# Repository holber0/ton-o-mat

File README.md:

# ton-O-mat
 ton-O-mat is a Interatcive sound generator that allows Kids to learn the one scale
 
## Inititial Setup
Enable SPI Bus:
```
sudo nano /boot/config.txt
```
Add following at the end of the File:
```
device_tree_param=spi=on
dtoverlay=spi-bcm2708
```
\
use `sudo raspi-config` to Enable „Advanced Options“ > „SPI“ restart afterwards `sudo reboot now`

## fluidsynth

fluidsynth is need as a background Service prividing a Midi Port for Pyton
```
fluidsynth -a alsa -m alsa_seq -i -l -s -g 1.0 /usr/share/sounds/sf2/FluidR3_GM.sf2
```

## Pyton Settings
\
the Virtual env "env" is used in ths Repo. Use `pip -r requirements.txt` to install all requirements\
if not install:
 
 ```
pip3 install virtualenv
pip install spidev
pip install mfrc522
 ```

source the activate file to switch to the venv 
```
source env/bin/activate
```

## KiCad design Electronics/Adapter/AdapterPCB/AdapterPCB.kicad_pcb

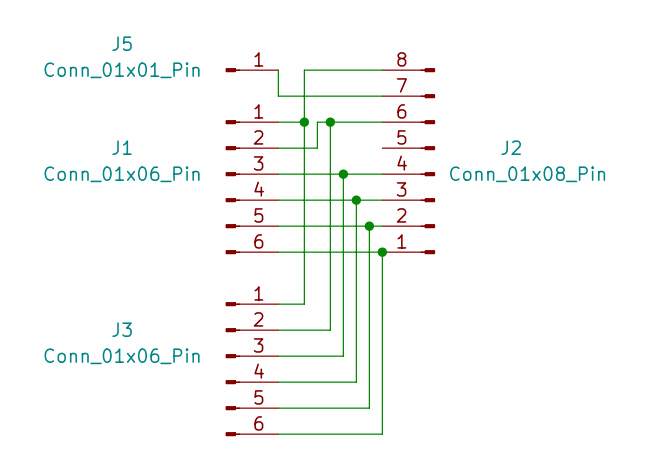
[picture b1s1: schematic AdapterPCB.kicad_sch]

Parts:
J1, J3: Conn_01x06_Pin; PinHeader_1x06_P2.54mm_Vertical
J2: Conn_01x08_Pin; PinHeader_1x08_P2.54mm_Vertical
J5: Conn_01x01_Pin; PinHeader_1x01_P2.54mm_Vertical

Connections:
unnamed: J1.1, J2.8, J3.1
unnamed: J1.2, J2.6, J3.2
unnamed: J1.3, J2.4, J3.3
unnamed: J1.4, J2.3, J3.4
unnamed: J1.5, J2.2, J3.5
unnamed: J1.6, J2.1, J3.6
unnamed: J2.7, J5.1

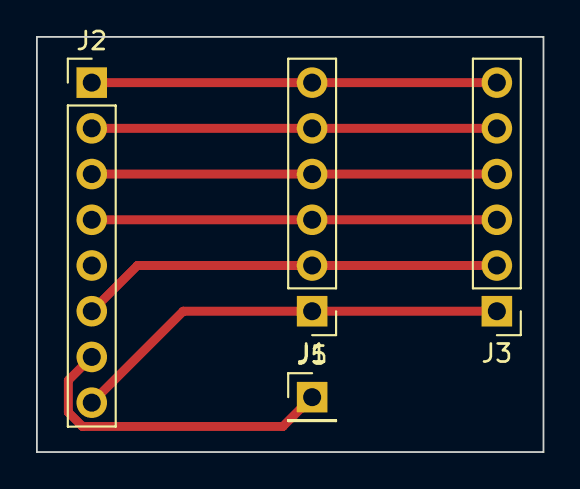
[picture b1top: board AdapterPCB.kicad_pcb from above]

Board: 2 copper layers, 28.1 x 23.1 mm, 4 parts (0 on the bottom side), 7 nets.

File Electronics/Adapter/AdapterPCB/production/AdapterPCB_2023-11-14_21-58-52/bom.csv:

Designator,Footprint,Quantity,Value,LCSC Part #
"J1, J3",PinHeader_1x06_P2.54mm_Vertical,2,Conn_01x06_Pin,
J2,PinHeader_1x08_P2.54mm_Vertical,1,Conn_01x08_Pin,
J5,PinHeader_1x01_P2.54mm_Vertical,1,Conn_01x01_Pin,

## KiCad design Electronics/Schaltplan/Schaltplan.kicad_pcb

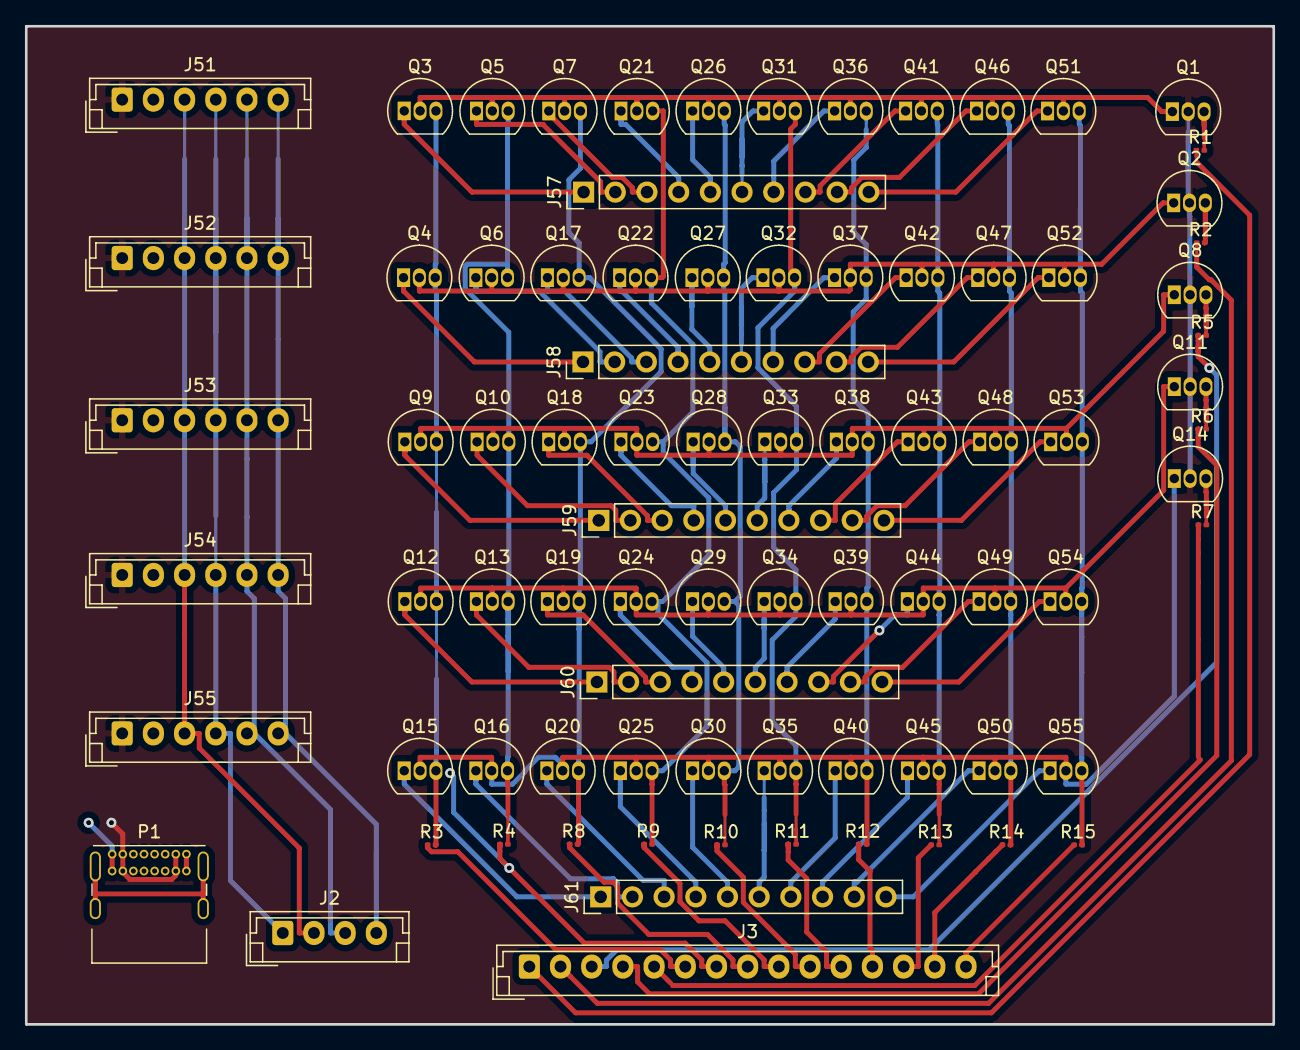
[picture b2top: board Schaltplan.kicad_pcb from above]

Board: 2 copper layers, 100.0 x 80.0 mm, 83 parts (0 on the bottom side), 91 nets.

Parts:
J2: Conn_01x04_Socket; JST_EH_B4B-EH-A_1x04_P2.50mm_Vertical
J3: Conn_01x15_Socket; JST_EH_B15B-EH-A_1x15_P2.50mm_Vertical
J51, J52, J53, J54, J55: Conn_01x06_Socket; JST_EH_B6B-EH-A_1x06_P2.50mm_Vertical
J57, J58, J59, J60, J61: Conn_01x10_Socket; PinHeader_1x10_P2.54mm_Vertical
P1: USB_C_Plug; USB_C_Receptacle_GCT_USB4085
Q1, Q2, Q3, Q4, Q5, Q6, Q7, Q8, Q9, Q10, Q11, Q12, Q13, Q14, Q15, Q16, Q17, Q18, Q19, Q20, Q21, Q22, Q23, Q24, Q25, Q26, Q27, Q28, Q29, Q30, Q31, Q32, Q33, Q34, Q35, Q36, Q37, Q38, Q39, Q40, Q41, Q42, Q43, Q44, Q45, Q46, Q47, Q48, Q49, Q50, Q51, Q52, Q53, Q54, Q55: 2SC1815; TO-92_Inline
R1, R2, R3, R4, R5, R6, R7, R8, R9, R10, R11, R12, R13, R14, R15: R; R_0201_0603Metric

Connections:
3,3V: J51.1, J52.1, J53.1, J54.1, J55.1, P1.A4 (VBUS), P1.A9 (VBUS), P1.B4 (VBUS), P1.B9 (VBUS), Q1.2 (C), Q2.2 (C), Q8.2 (C), Q11.2 (C), Q14.2 (C)
GND: J51.2, J52.2, J53.2, J54.2, J55.2, P1.A1 (GND), P1.A12 (GND), P1.B1 (GND), P1.B12 (GND)
GPIO00: J3.1, R1.1
GPIO01: J3.2, R2.1
GPIO02: J3.3, R5.1
GPIO03: J3.4, R6.1
GPIO04: J3.5, R7.1
GPIO05: J3.6, R3.1
GPIO06: J3.7, R4.1
GPIO07: J3.8, R8.1
GPIO08: J3.9, R9.1
GPIO09: J3.10, R10.1
GPIO10: J3.11, R11.1
GPIO11: J3.12, R12.1
GPIO12: J3.13, R13.1
GPIO13: J3.14, R14.1
GPIO14: J3.15, R15.1
MISO: J2.2, J51.3, J52.3, J53.3, J54.3, J55.3
MOSI: J2.1, J51.4, J52.4, J53.4, J54.4, J55.4
unnamed: Q1.3 (B), R1.2
unnamed: Q1.1 (E), Q3.2 (C), Q5.2 (C), Q7.2 (C), Q21.2 (C), Q26.2 (C), Q31.2 (C), Q36.2 (C), Q41.2 (C), Q46.2 (C), Q51.2 (C)
unnamed: Q2.3 (B), R2.2
unnamed: Q8.3 (B), R5.2
unnamed: Q5.3 (B), Q6.3 (B), Q10.3 (B), Q13.3 (B), Q16.3 (B), R4.2
unnamed: Q8.1 (E), Q9.2 (C), Q10.2 (C), Q18.2 (C), Q23.2 (C), Q28.2 (C), Q33.2 (C), Q38.2 (C), Q43.2 (C), Q48.2 (C), Q53.2 (C)
unnamed: Q11.3 (B), R6.2
unnamed: Q11.1 (E), Q12.2 (C), Q13.2 (C), Q19.2 (C), Q24.2 (C), Q29.2 (C), Q34.2 (C), Q39.2 (C), Q44.2 (C), Q49.2 (C), Q54.2 (C)
unnamed: Q3.3 (B), Q4.3 (B), Q9.3 (B), Q12.3 (B), Q15.3 (B), R3.2
unnamed: Q14.3 (B), R7.2
unnamed: Q14.1 (E), Q15.2 (C), Q16.2 (C), Q20.2 (C), Q25.2 (C), Q30.2 (C), Q35.2 (C), Q40.2 (C), Q45.2 (C), Q50.2 (C), Q55.2 (C)
unnamed: Q7.3 (B), Q17.3 (B), Q18.3 (B), Q19.3 (B), Q20.3 (B), R8.2
unnamed: Q2.1 (E), Q4.2 (C), Q6.2 (C), Q17.2 (C), Q22.2 (C), Q27.2 (C), Q32.2 (C), Q37.2 (C), Q42.2 (C), Q47.2 (C), Q52.2 (C)
unnamed: Q21.3 (B), Q22.3 (B), Q23.3 (B), Q24.3 (B), Q25.3 (B), R9.2
unnamed: Q26.3 (B), Q27.3 (B), Q28.3 (B), Q29.3 (B), Q30.3 (B), R10.2
unnamed: Q31.3 (B), Q32.3 (B), Q33.3 (B), Q34.3 (B), Q35.3 (B), R11.2
unnamed: Q36.3 (B), Q37.3 (B), Q38.3 (B), Q39.3 (B), Q40.3 (B), R12.2
unnamed: Q41.3 (B), Q42.3 (B), Q43.3 (B), Q44.3 (B), Q45.3 (B), R13.2
unnamed: Q46.3 (B), Q47.3 (B), Q48.3 (B), Q49.3 (B), Q50.3 (B), R14.2
unnamed: Q51.3 (B), Q52.3 (B), Q53.3 (B), Q54.3 (B), Q55.3 (B), R15.2
RST01: J57.1, Q3.1 (E)
RST02: J57.2, Q5.1 (E)
RST03: J57.3, Q7.1 (E)
RST04: J57.4, Q21.1 (E)
RST05: J57.5, Q26.1 (E)
RST06: J57.6, Q31.1 (E)
RST07: J57.7, Q36.1 (E)
RST08: J57.8, Q41.1 (E)
RST09: J57.9, Q46.1 (E)
RST10: J57.10, Q51.1 (E)
RST11: J58.1, Q4.1 (E)
RST12: J58.2, Q6.1 (E)
RST13: J58.3, Q17.1 (E)
RST14: J58.4, Q22.1 (E)
RST15: J58.5, Q27.1 (E)
RST16: J58.6, Q32.1 (E)
RST17: J58.7, Q37.1 (E)
RST18: J58.8, Q42.1 (E)
RST19: J58.9, Q47.1 (E)
RST20: J58.10, Q52.1 (E)
RST21: J59.1, Q9.1 (E)
RST22: J59.2, Q10.1 (E)
RST23: J59.3, Q18.1 (E)
RST24: J59.4, Q23.1 (E)
RST25: J59.5, Q28.1 (E)
RST26: J59.6, Q33.1 (E)
RST27: J59.7, Q38.1 (E)
RST28: J59.8, Q43.1 (E)
RST29: J59.9, Q48.1 (E)
RST30: J59.10, Q53.1 (E)
RST31: J60.1, Q12.1 (E)
RST32: J60.2, Q13.1 (E)
RST33: J60.3, Q19.1 (E)
RST34: J60.4, Q24.1 (E)
RST35: J60.5, Q29.1 (E)
RST36: J60.6, Q34.1 (E)
RST37: J60.7, Q39.1 (E)
RST38: J60.8, Q44.1 (E)
RST39: J60.9, Q49.1 (E)
RST40: J60.10, Q54.1 (E)
RST41: J61.1, Q15.1 (E)
RST42: J61.2, Q16.1 (E)
RST43: J61.3, Q20.1 (E)
RST44: J61.4, Q25.1 (E)
RST45: J61.5, Q30.1 (E)
RST46: J61.6, Q35.1 (E)
RST47: J61.7, Q40.1 (E)
RST48: J61.8, Q45.1 (E)
RST49: J61.9, Q50.1 (E)
RST50: J61.10, Q55.1 (E)
SCK: J2.3, J51.5, J52.5, J53.5, J54.5, J55.5
SDA: J2.4, J51.6, J52.6, J53.6, J54.6, J55.6

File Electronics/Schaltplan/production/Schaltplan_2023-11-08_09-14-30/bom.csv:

Designator,Footprint,Quantity,Value,LCSC Part #
J2,JST_EH_B4B-EH-A_1x04_P2.50mm_Vertical,1,Conn_01x04_Socket,
J3,JST_EH_B15B-EH-A_1x15_P2.50mm_Vertical,1,Conn_01x15_Socket,
"J51, J52, J53, J54, J55",JST_EH_B6B-EH-A_1x06_P2.50mm_Vertical,5,Conn_01x06_Socket,
"J57, J58, J59, J60, J61",PinHeader_1x10_P2.54mm_Vertical,5,Conn_01x10_Socket,
P1,USB_C_Receptacle_GCT_USB4085,1,USB_C_Plug,
"Q1, Q10, Q11, Q12, Q13, Q14, Q15, Q16, Q17, Q18, Q19, Q2, Q20, Q21, Q22, Q23, Q24, Q25, Q26, Q27, Q28, Q29, Q3, Q30, Q31, Q32, Q33, Q34, Q35, Q36, Q37, Q38, Q39, Q4, Q40, Q41, Q42, Q43, Q44, Q45, Q46, Q47, Q48, Q49, Q5, Q50, Q51, Q52, Q53, Q54, Q55, Q6, Q7, Q8, Q9",TO-92_Inline,55,2SC1815,
"R1, R10, R11, R12, R13, R14, R15, R2, R3, R4, R5, R6, R7, R8, R9",0201,15,R,

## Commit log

2023-09-22 init commit
2023-09-22 added Readme
2023-09-26 added venv and requirements.txt
2023-10-03 first try to use multipe readers
2023-10-03 dummy schaltung zwiwschen den readern
2023-10-04 added Matrix Support to Read Chips
2023-10-04 fixed Matrix to use Raspi default GPIOs
2023-10-04 fixed Import bug
2023-10-04 performance tuning
2023-10-04 added Debug opption
2023-10-04 fixed Typo
2023-10-10 added config File vor Setting
2023-10-10 added MP3 Assets
2023-10-10 first try to get the sound Logic
2023-10-11 added Tone Selector
2023-10-11 added play sound
2023-11-06 changed Config
2023-11-06 Added Python Play Sound
2023-11-06 Integrated PlaySound to Main
2023-11-06 Fixed Config Naming
2023-11-06 change Col by Col Read
2023-11-06 fixed Michi fault
2023-11-06 change palySound to use a background Service
2023-11-06 pip freeze
2023-11-06 README
2023-11-06 added Launch File for autostart via crontab
2023-11-06 fixed unused Deps
2023-11-07 first try to use local mp3s
2023-11-07 local soundfiles
2023-11-07 added local mp3 Files
2023-11-07 fixed direct mp3 play
2023-11-07 added RFID IDs
2023-11-07 Noten hochgeladen
    Noten sind bestellt und werden mit SLS aus Nylon gedruckt.
2023-12-02 Raspi is working with adruino
2023-12-02 added Adruino Code that must run on a Mega
2023-12-08 added autostoart and fixed Int to string
2023-12-08 auto restart, fixing open files error
2023-12-08 fixed Pin Order
2023-12-08 Revert "auto restart, fixing open files error"
    This reverts commit 48ac6fb1ee783a5d6972f78e8762d634a0cbd1ef.
2023-12-08 fixed some bugs, autostart with restart
2023-12-08 fixed launcher
2023-12-17 Revers Order for GPIOs
2023-12-17 fixed to set all off
2023-12-17 fixed first init
2023-12-18 Update config.json
    Added new RFID chip
2024-01-12 Added electronics
    Electronic files for manufacturing
